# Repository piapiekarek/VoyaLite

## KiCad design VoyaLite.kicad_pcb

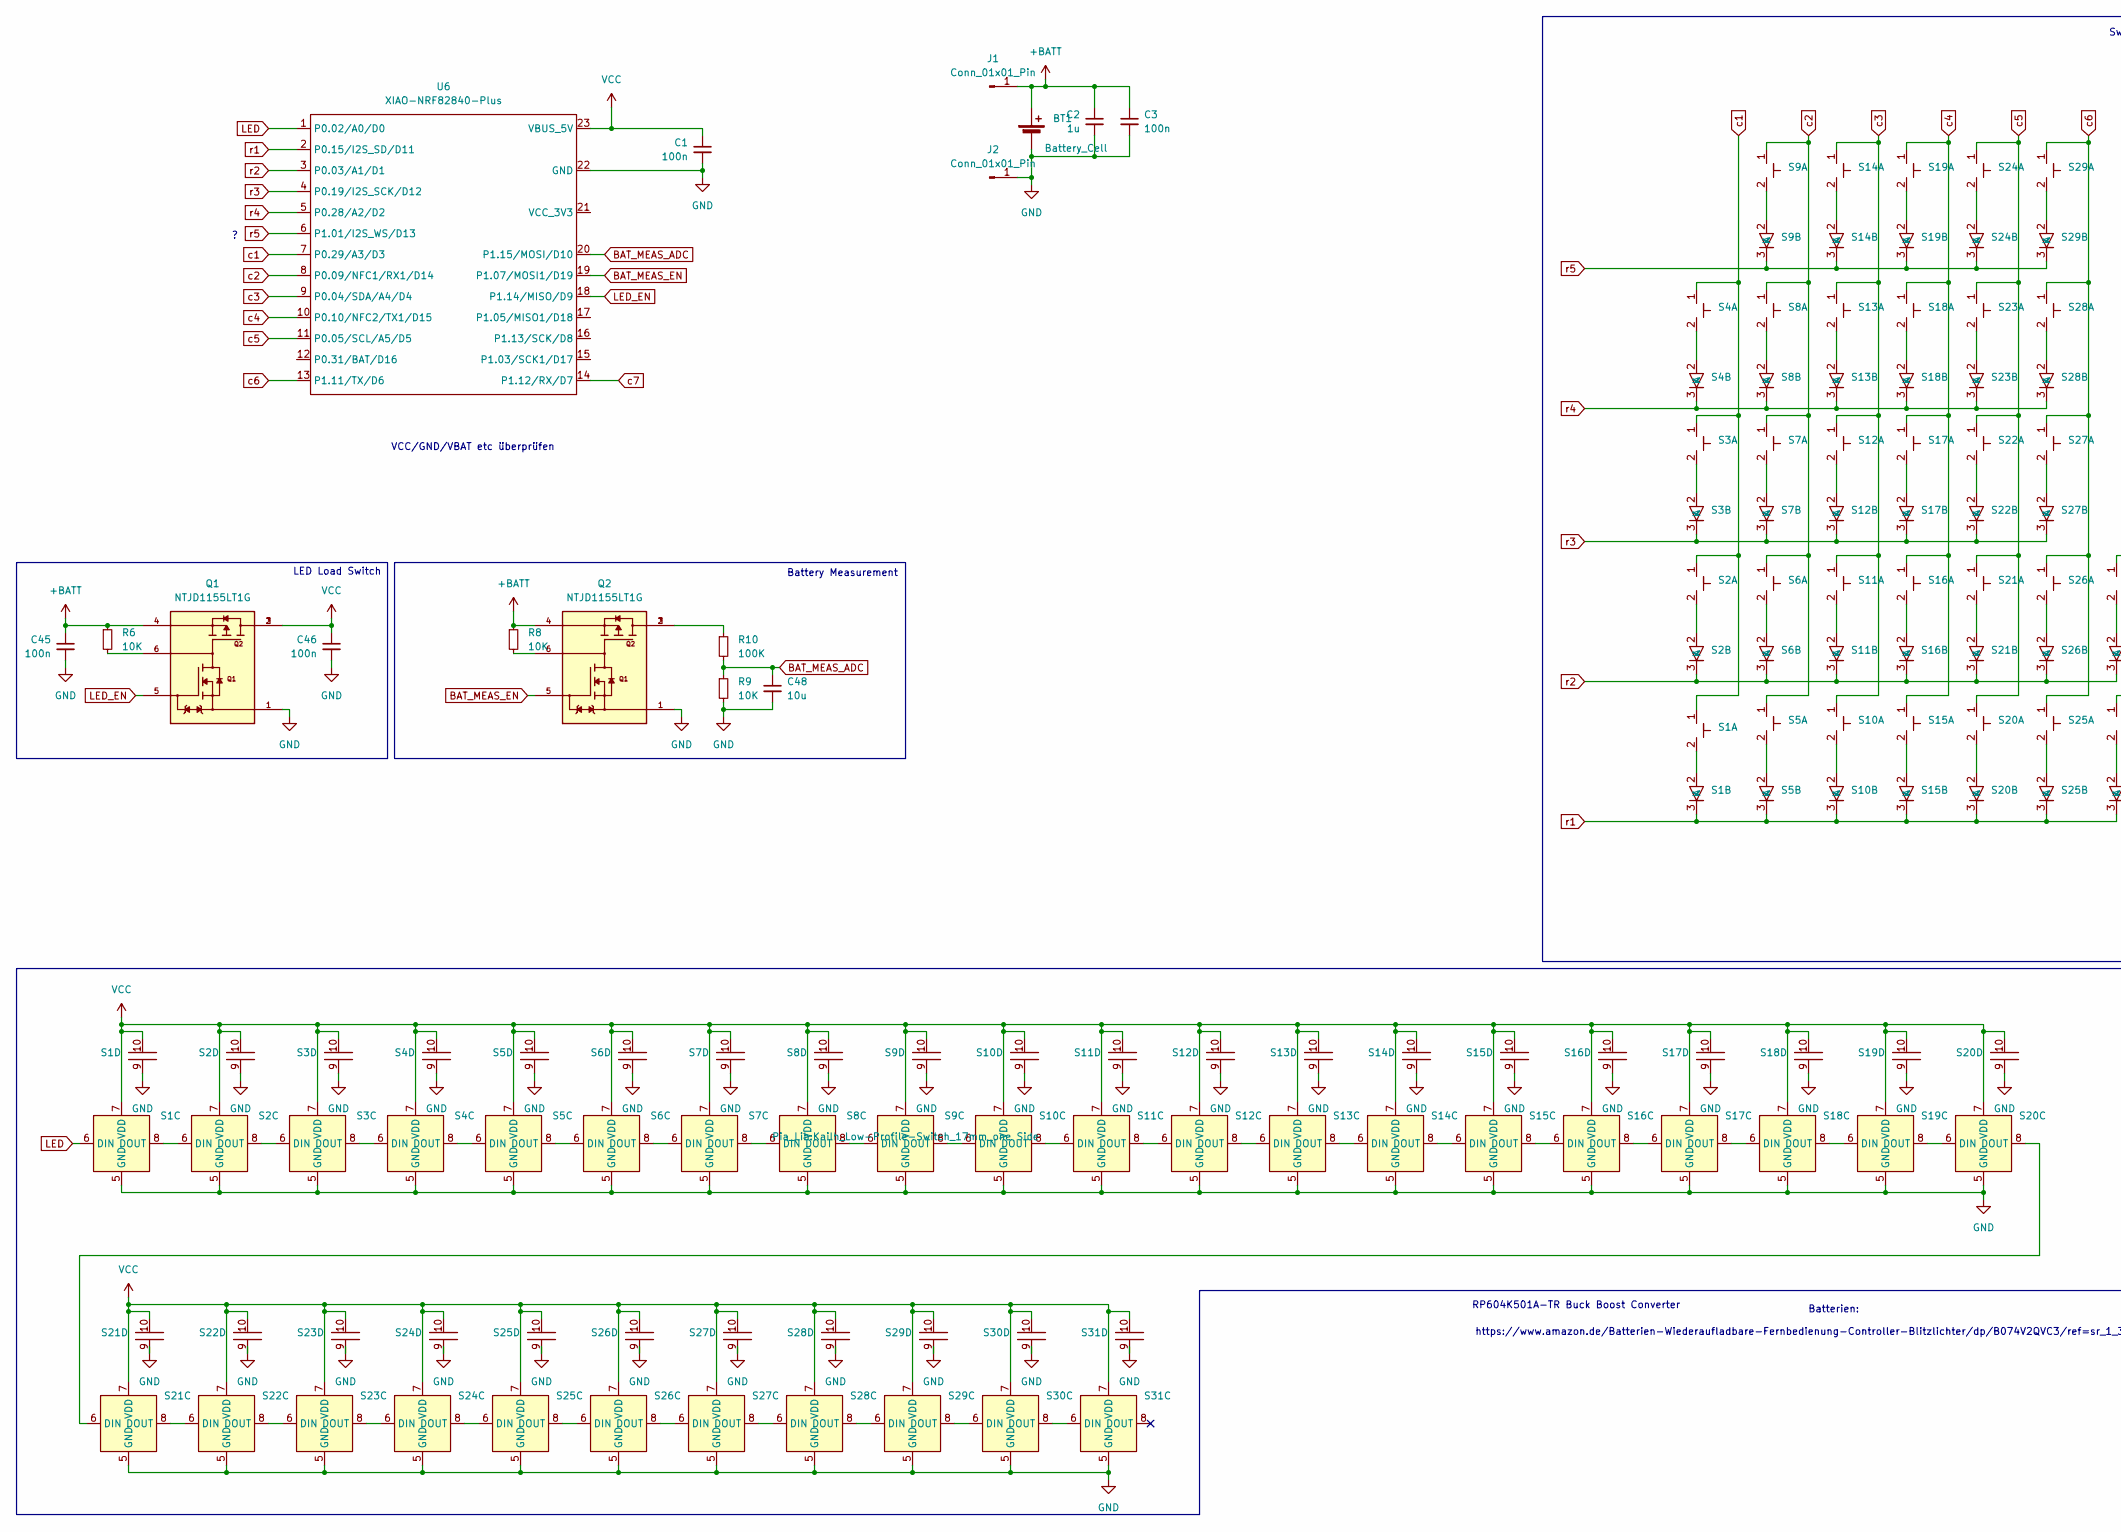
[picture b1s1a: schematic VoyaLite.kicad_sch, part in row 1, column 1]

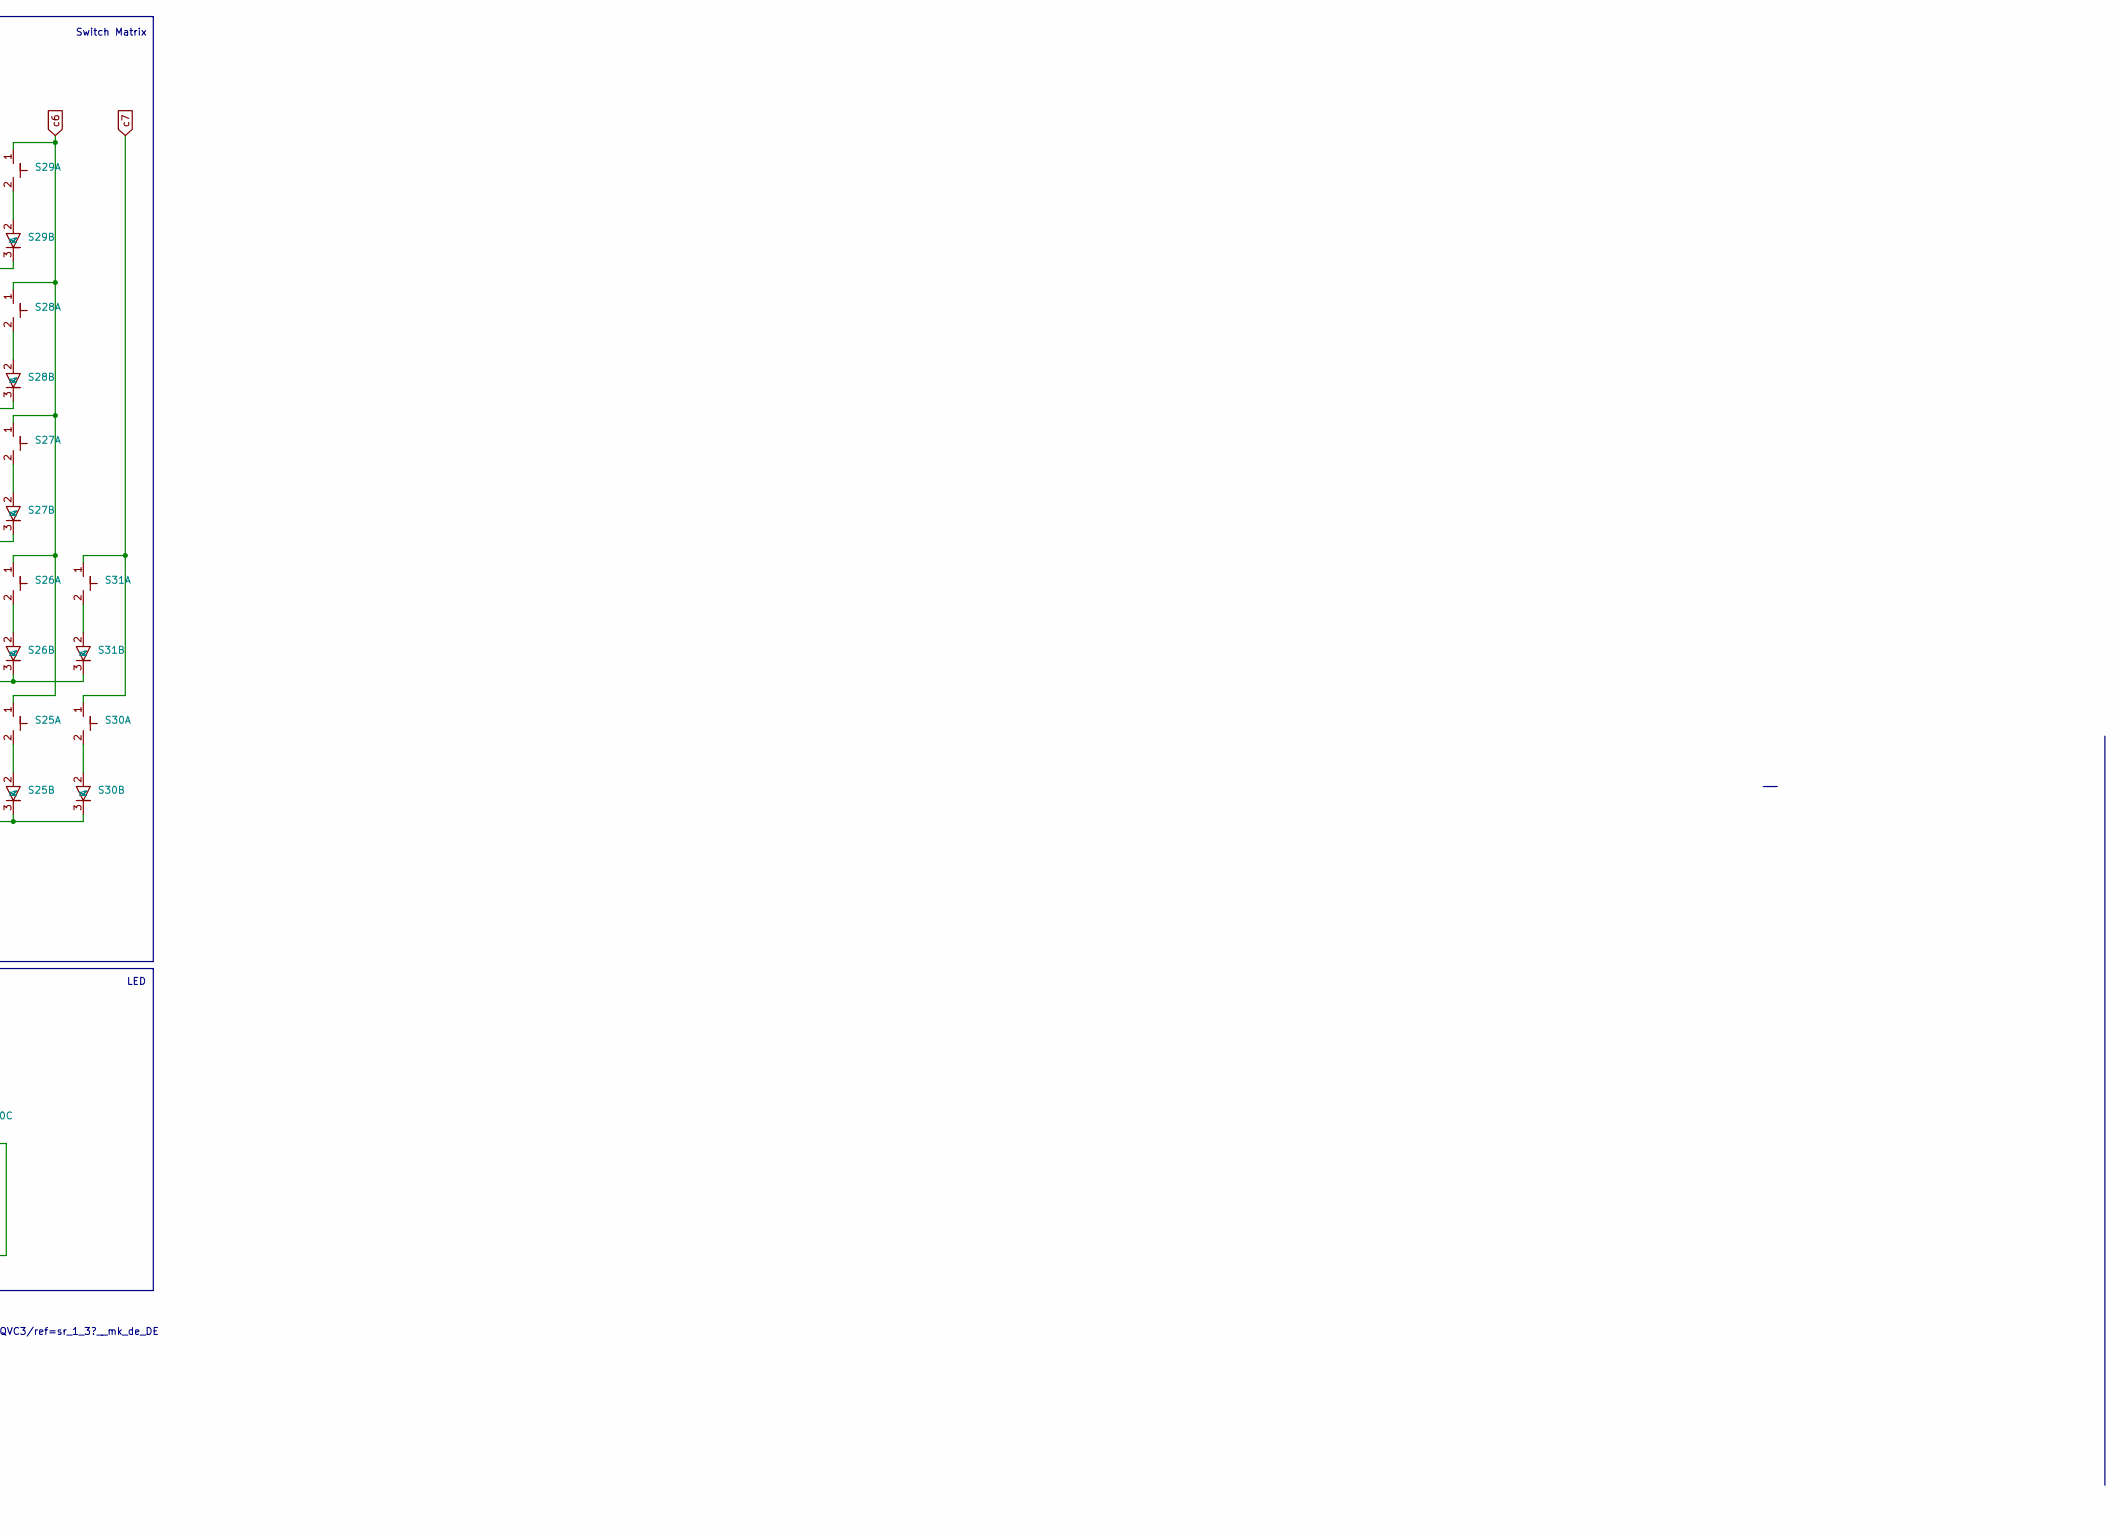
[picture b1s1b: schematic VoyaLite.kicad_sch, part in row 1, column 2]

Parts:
BT1: Battery_Cell; Batteriehalter AAA_Metall
C1, C3, C45, C46: 100n; C_0402_1005Metric_Pad0.74x0.62mm_HandSolder
C2: 1u; C_0402_1005Metric_Pad0.74x0.62mm_HandSolder
C48: 10u; C_0603_1608Metric_Pad1.08x0.95mm_HandSolder
J1, J2: Conn_01x01_Pin; Testpoint-pad
Q1, Q2: NTJD1155LT1G; TRANS_NTJD1155LT1G; PARTREV Rev. 6
R6, R8, R9: 10K; C_0402_1005Metric_Pad0.74x0.62mm_HandSolder
R10: 100K; C_0402_1005Metric_Pad0.74x0.62mm_HandSolder
S1, S2, S3, S4, S5, S6, S7, S8, S9, S10, S11, S12, S13, S14, S15, S16, S17, S18, S19, S20, S21, S22, S23, S24, S25, S26, S27, S28, S29, S30, S31: Kailh_Low-Profile-Switch_17mm_one Side
U6: XIAO-NRF82840-Plus; MCU_Seeed_nRF52840

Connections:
+BATT: BT1.1 (+), C2.1, C3.1, C45.1, J1.1, Q1.4, Q2.4, R6.1, R8.1
BAT_MEAS_ADC: C48.1, R9.1, R10.2, U6.20 (P1.15/MOSI/D10)
BAT_MEAS_EN: Q2.5, U6.19 (P1.07/MOSI1/D19)
GND: BT1.2 (-), C1.2, C2.2, C3.2, C45.2, C46.2, C48.2, J2.1, Q1.1, Q2.1, R9.2, S1.5 (GND), S1.9, S2.5 (GND), S2.9, S3.5 (GND), S3.9, S4.5 (GND), S4.9, S5.5 (GND), S5.9, S6.5 (GND), S6.9, S7.5 (GND), S7.9, S8.5 (GND), S8.9, S9.5 (GND), S9.9, S10.5 (GND), S10.9, S11.5 (GND), S11.9, S12.5 (GND), S12.9, S13.5 (GND), S13.9, S14.5 (GND), S14.9, S15.5 (GND), S15.9, S16.5 (GND), S16.9, S17.5 (GND), S17.9, S18.5 (GND), S18.9, S19.5 (GND), S19.9, S20.5 (GND), S20.9, S21.5 (GND), S21.9, S22.5 (GND), S22.9, S23.5 (GND), S23.9, S24.5 (GND), S24.9, S25.5 (GND), S25.9, S26.5 (GND), S26.9, S27.5 (GND), S27.9, S28.5 (GND), S28.9, S29.5 (GND), S29.9, S30.5 (GND), S30.9, S31.5 (GND), S31.9, U6.22 (GND)
LED: S1.6 (DIN), U6.1 (P0.02/A0/D0)
LED_EN: Q1.5, U6.18 (P1.14/MISO/D9)
unnamed: Q1.6, R6.2
unnamed: Q2.2, Q2.3, R10.1
unnamed: Q2.6, R8.2
unnamed: S1.8 (DOUT), S2.6 (DIN)
unnamed: S2.8 (DOUT), S3.6 (DIN)
unnamed: S3.8 (DOUT), S4.6 (DIN)
unnamed: S4.8 (DOUT), S5.6 (DIN)
unnamed: S5.8 (DOUT), S6.6 (DIN)
unnamed: S6.8 (DOUT), S7.6 (DIN)
unnamed: S7.8 (DOUT), S8.6 (DIN)
unnamed: S8.8 (DOUT), S9.6 (DIN)
unnamed: S9.8 (DOUT), S10.6 (DIN)
unnamed: S10.8 (DOUT), S11.6 (DIN)
unnamed: S11.8 (DOUT), S12.6 (DIN)
unnamed: S12.8 (DOUT), S13.6 (DIN)
unnamed: S13.8 (DOUT), S14.6 (DIN)
unnamed: S14.8 (DOUT), S15.6 (DIN)
unnamed: S15.8 (DOUT), S16.6 (DIN)
unnamed: S16.8 (DOUT), S17.6 (DIN)
unnamed: S17.8 (DOUT), S18.6 (DIN)
unnamed: S18.8 (DOUT), S19.6 (DIN)
unnamed: S19.8 (DOUT), S20.6 (DIN)
unnamed: S20.8 (DOUT), S21.6 (DIN)
unnamed: S21.8 (DOUT), S22.6 (DIN)
unnamed: S22.8 (DOUT), S23.6 (DIN)
unnamed: S23.8 (DOUT), S24.6 (DIN)
unnamed: S24.8 (DOUT), S25.6 (DIN)
unnamed: S25.8 (DOUT), S26.6 (DIN)
unnamed: S26.8 (DOUT), S27.6 (DIN)
unnamed: S27.8 (DOUT), S28.6 (DIN)
unnamed: S28.8 (DOUT), S29.6 (DIN)
unnamed: S29.8 (DOUT), S30.6 (DIN)
unnamed: S30.8 (DOUT), S31.6 (DIN)
VCC: C1.1, C46.1, Q1.2, Q1.3, S1.7 (VDD), S1.10, S2.7 (VDD), S2.10, S3.7 (VDD), S3.10, S4.7 (VDD), S4.10, S5.7 (VDD), S5.10, S6.7 (VDD), S6.10, S7.7 (VDD), S7.10, S8.7 (VDD), S8.10, S9.7 (VDD), S9.10, S10.7 (VDD), S10.10, S11.7 (VDD), S11.10, S12.7 (VDD), S12.10, S13.7 (VDD), S13.10, S14.7 (VDD), S14.10, S15.7 (VDD), S15.10, S16.7 (VDD), S16.10, S17.7 (VDD), S17.10, S18.7 (VDD), S18.10, S19.7 (VDD), S19.10, S20.7 (VDD), S20.10, S21.7 (VDD), S21.10, S22.7 (VDD), S22.10, S23.7 (VDD), S23.10, S24.7 (VDD), S24.10, S25.7 (VDD), S25.10, S26.7 (VDD), S26.10, S27.7 (VDD), S27.10, S28.7 (VDD), S28.10, S29.7 (VDD), S29.10, S30.7 (VDD), S30.10, S31.7 (VDD), S31.10, U6.23 (VBUS_5V)
c1: S1.1, S2.1, S3.1, S4.1, U6.7 (P0.29/A3/D3)
c2: S5.1, S6.1, S7.1, S8.1, S9.1, U6.8 (P0.09/NFC1/RX1/D14)
c3: S10.1, S11.1, S12.1, S13.1, S14.1, U6.9 (P0.04/SDA/A4/D4)
c4: S15.1, S16.1, S17.1, S18.1, S19.1, U6.10 (P0.10/NFC2/TX1/D15)
c5: S20.1, S21.1, S22.1, S23.1, S24.1, U6.11 (P0.05/SCL/A5/D5)
c6: S25.1, S26.1, S27.1, S28.1, S29.1, U6.13 (P1.11/TX/D6)
c7: S30.1, S31.1, U6.14 (P1.12/RX/D7)
r1: S1.3 (K), S5.3 (K), S10.3 (K), S15.3 (K), S20.3 (K), S25.3 (K), S30.3 (K), U6.2 (P0.15/I2S_SD/D11)
r2: S2.3 (K), S6.3 (K), S11.3 (K), S16.3 (K), S21.3 (K), S26.3 (K), S31.3 (K), U6.3 (P0.03/A1/D1)
r3: S3.3 (K), S7.3 (K), S12.3 (K), S17.3 (K), S22.3 (K), S27.3 (K), U6.4 (P0.19/I2S_SCK/D12)
r4: S4.3 (K), S8.3 (K), S13.3 (K), S18.3 (K), S23.3 (K), S28.3 (K), U6.5 (P0.28/A2/D2)
r5: S9.3 (K), S14.3 (K), S19.3 (K), S24.3 (K), S29.3 (K), U6.6 (P1.01/I2S_WS/D13)

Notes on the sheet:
VCC/GND/VBAT etc überprüfen
Battery Measurement
Batterien: https://www.amazon.de/Batterien-Wiederaufladbare-Fernbedienung-Controller-Blitzlichter/dp/B074V2QVC3/ref=sr_1_3?__mk_de_DE
LED Load Switch
LED
Switch Matrix
RP604K501A-TR Buck Boost Converter

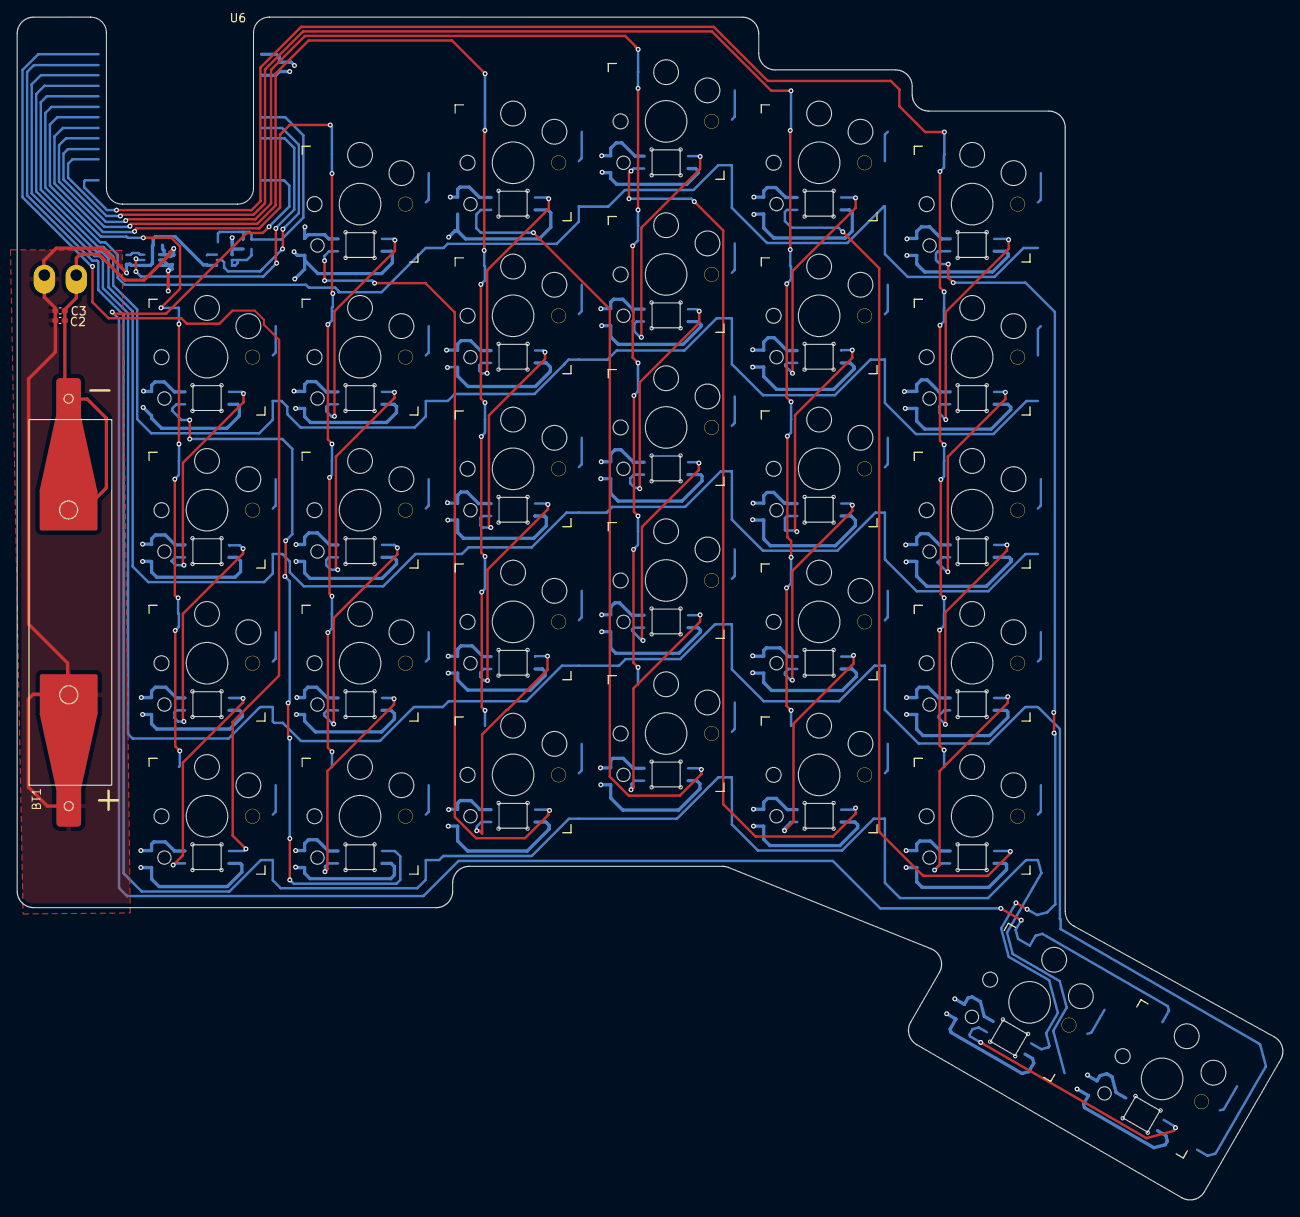
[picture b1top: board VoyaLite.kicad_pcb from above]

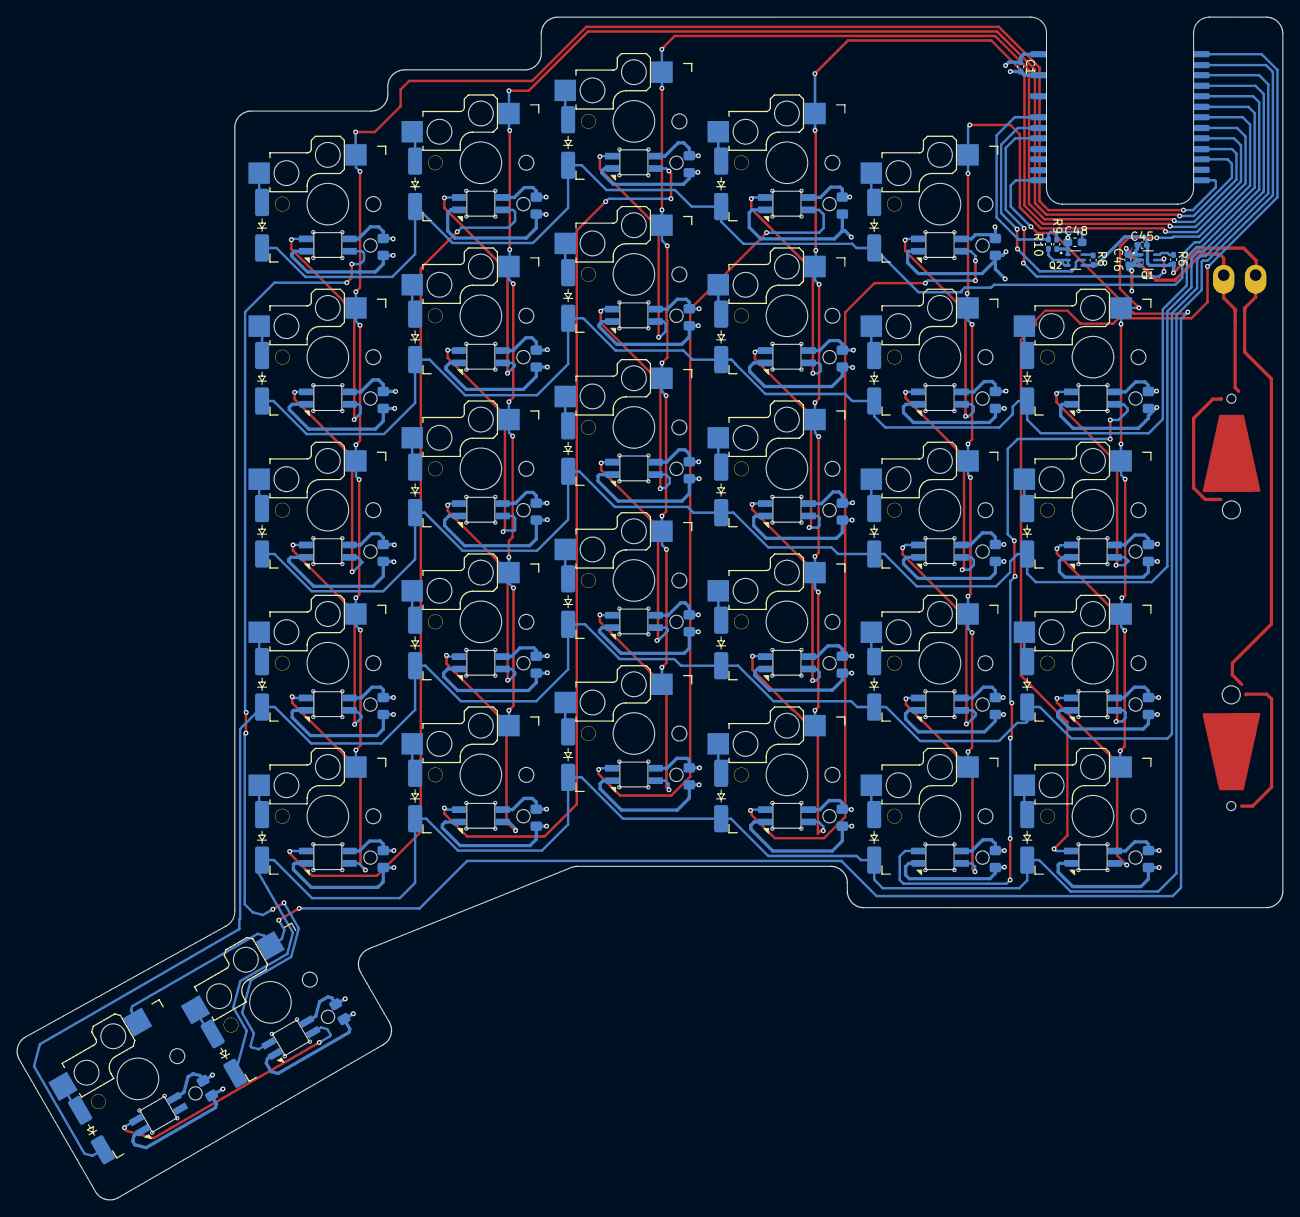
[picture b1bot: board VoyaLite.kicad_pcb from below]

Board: 4 copper layers, 153.0 x 143.0 mm, 47 parts (12 on the bottom side), 52 nets.

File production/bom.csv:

Designator,Footprint,Quantity,Value,LCSC Part #
BT1,Batteriehalter AAA_Metall,1,Battery_Cell,
"C1, C3, C45, C46",0402,4,100n,
C2,0402,1,1u,
C48,0603,1,10u,
"J1, J2",Testpoint-pad,2,Conn_01x01_Pin,
"Q1, Q2",TRANS_NTJD1155LT1G,2,NTJD1155LT1G,
R10,0402,1,100K,
"R6, R8, R9",0402,3,10K,
"S1, S10, S11, S12, S13, S14, S15, S16, S17, S18, S19, S2, S20, S21, S22, S23, S24, S25, S26, S27, S28, S29, S3, S30, S31, S4, S5, S6, S7, S8, S9",Kailh_Low-Profile-Switch_17mm_one Side,31,~,
U6,MCU_Seeed_nRF52840,1,XIAO-NRF82840-Plus,

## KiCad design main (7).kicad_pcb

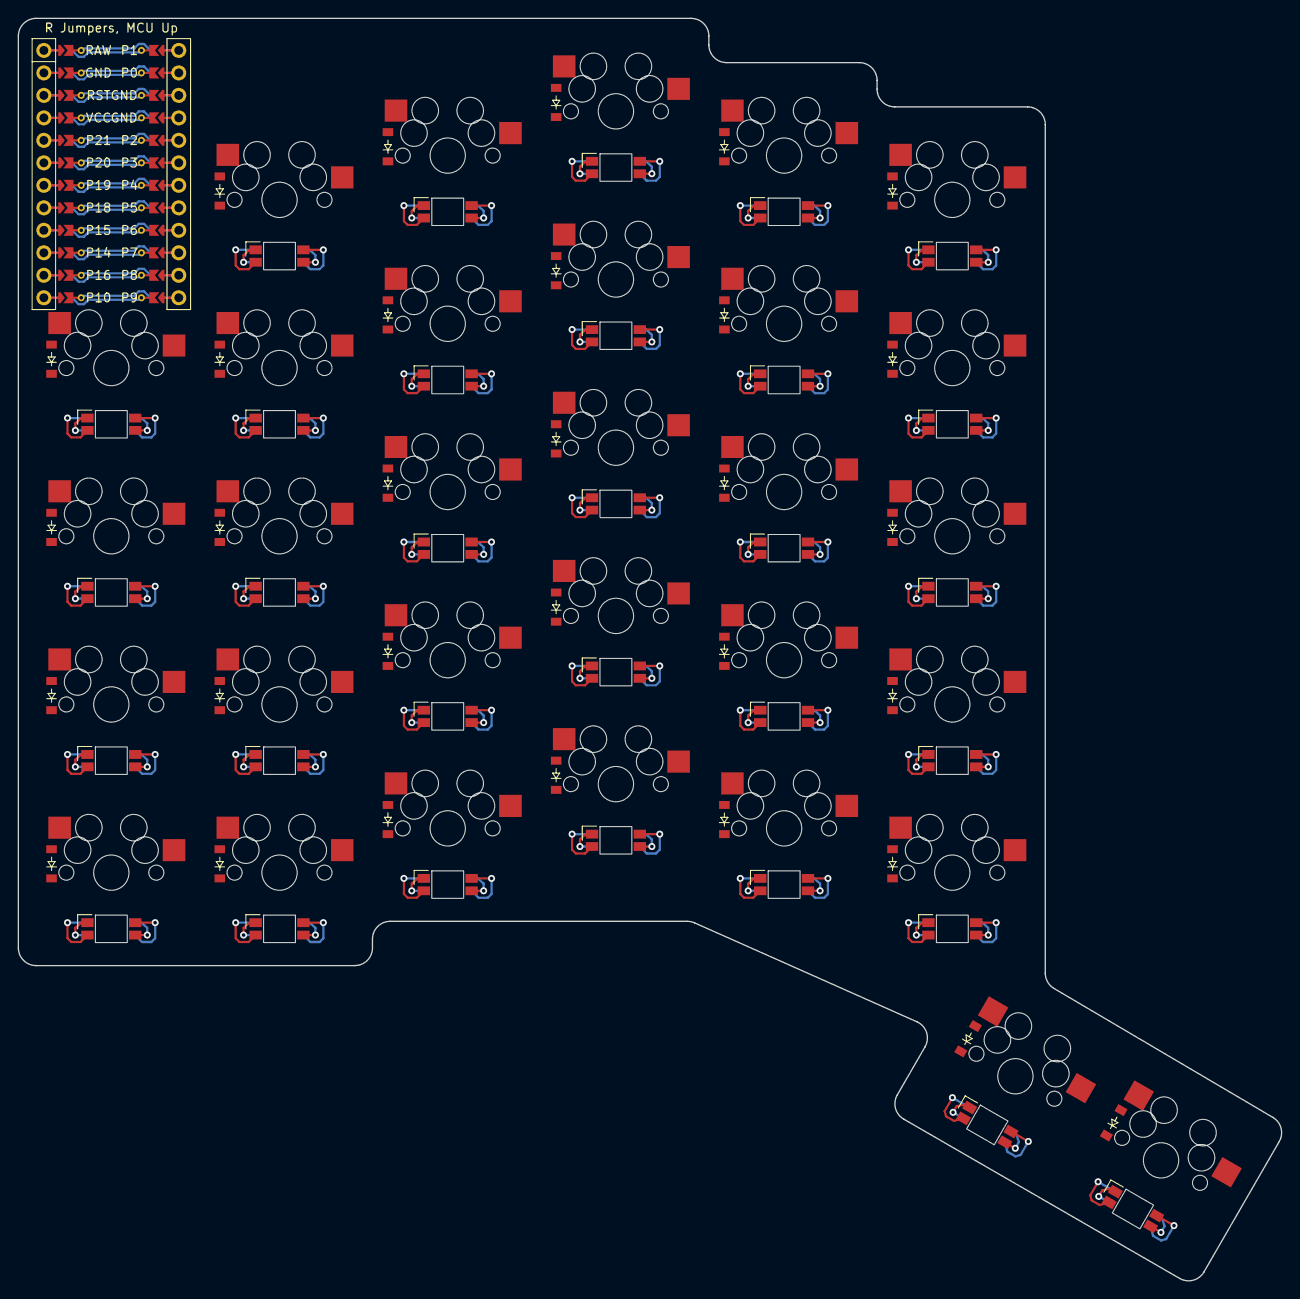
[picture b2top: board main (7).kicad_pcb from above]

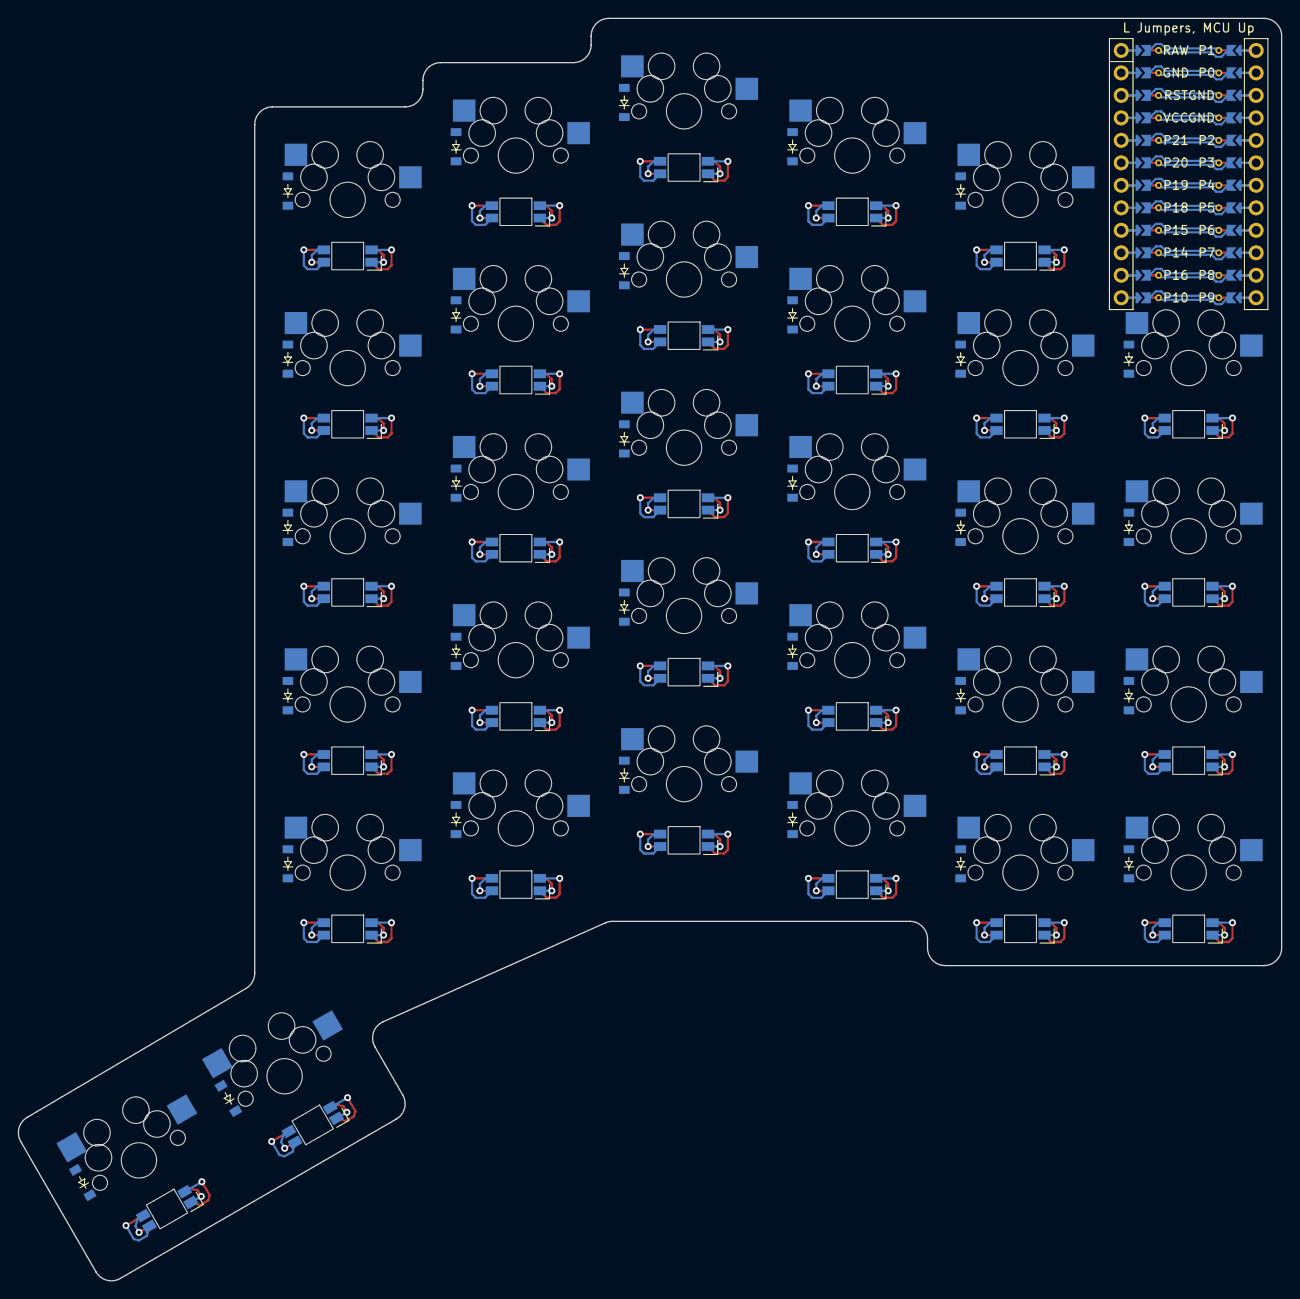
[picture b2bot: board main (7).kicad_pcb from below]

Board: 2 copper layers, 142.7 x 142.6 mm, 125 parts (62 on the bottom side), 69 nets.

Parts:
D1, D2, D3, D4, D5, D6, D7, D8, D9, D10, D11, D12, D13, D14, D15, D16, D17, D18, D19, D20, D21, D22, D23, D24, D25, D26, D27, D28, D29, D30, D31, D32, D33, D34, D35, D36, D37, D38, D39, D40, D41, D42, D43, D44, D45, D46, D47, D48, D49, D50, D51, D52, D53, D54, D55, D56, D57, D58, D59, D60, D61, D62: diode_tht_sod123
LED1, LED2, LED3, LED4, LED5, LED6, LED7, LED8, LED9, LED10, LED11, LED12, LED13, LED14, LED15, LED16, LED17, LED18, LED19, LED20, LED21, LED22, LED23, LED24, LED25, LED26, LED27, LED28, LED29, LED30, LED31: led_SK6812mini-e (underglow, reversible)
MCU1: mcu_nice_nano
S1, S2, S3, S4, S5, S6, S7, S8, S9, S10, S11, S12, S13, S14, S15, S16, S17, S18, S19, S20, S21, S22, S23, S24, S25, S26, S27, S28, S29, S30, S31: MX

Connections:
GND: LED1.3, LED2.3, LED3.3, LED4.3, LED5.3, LED6.3, LED7.3, LED8.3, LED9.3, LED10.3, LED11.3, LED12.3, LED13.3, LED14.3, LED15.3, LED16.3, LED17.3, LED18.3, LED19.3, LED20.3, LED21.3, LED22.3, LED23.3, LED24.3, LED25.3, LED26.3, LED27.3, LED28.3, LED29.3, LED30.3, LED31.3, MCU1.103, MCU1.104, MCU1.123
LED_2: LED1.2, LED2.4
LED_3: LED2.2, LED3.4
LED_4: LED3.2, LED4.4
LED_5: LED4.2, LED5.4
LED_6: LED5.2, LED6.4
LED_7: LED6.2, LED7.4
LED_8: LED7.2, LED8.4
LED_9: LED8.2, LED9.4
LED_10: LED9.2, LED10.4
LED_11: LED10.2, LED11.4
LED_12: LED11.2, LED12.4
LED_13: LED12.2, LED13.4
LED_14: LED13.2, LED14.4
LED_15: LED14.2, LED15.4
LED_16: LED15.2, LED16.4
LED_17: LED16.2, LED17.4
LED_18: LED17.2, LED18.4
LED_19: LED18.2, LED19.4
LED_20: LED19.2, LED20.4
LED_21: LED20.2, LED21.4
LED_22: LED21.2, LED22.4
LED_23: LED22.2, LED23.4
LED_24: LED23.2, LED24.4
LED_25: LED24.2, LED25.4
LED_26: LED25.2, LED26.4
LED_27: LED26.2, LED27.4
LED_28: LED27.2, LED28.4
LED_29: LED28.2, LED29.4
LED_30: LED29.2, LED30.4
LED_31: LED30.2, LED31.4
VCC: LED1.1, LED2.1, LED3.1, LED4.1, LED5.1, LED6.1, LED7.1, LED8.1, LED9.1, LED10.1, LED11.1, LED12.1, LED13.1, LED14.1, LED15.1, LED16.1, LED17.1, LED18.1, LED19.1, LED20.1, LED21.1, LED22.1, LED23.1, LED24.1, LED25.1, LED26.1, LED27.1, LED28.1, LED29.1, LED30.1, LED31.1, MCU1.121
c1_r2: D4.2, D35.2, S4.2
c1_r3: D3.2, D34.2, S3.2
c1_r4: D2.2, D33.2, S2.2
c1_r5: D1.2, D32.2, S1.2
c2_r1: D9.2, D40.2, S9.2
c2_r2: D8.2, D39.2, S8.2
c2_r3: D7.2, D38.2, S7.2
c2_r4: D6.2, D37.2, S6.2
c2_r5: D5.2, D36.2, S5.2
c3_r1: D14.2, D45.2, S14.2
c3_r2: D13.2, D44.2, S13.2
c3_r3: D12.2, D43.2, S12.2
c3_r4: D11.2, D42.2, S11.2
c3_r5: D10.2, D41.2, S10.2
c4_r1: D19.2, D50.2, S19.2
c4_r2: D18.2, D49.2, S18.2
c4_r3: D17.2, D48.2, S17.2
c4_r4: D16.2, D47.2, S16.2
c4_r5: D15.2, D46.2, S15.2
c5_r1: D24.2, D55.2, S24.2
c5_r2: D23.2, D54.2, S23.2
c5_r3: D22.2, D53.2, S22.2
c5_r4: D21.2, D52.2, S21.2
c5_r5: D20.2, D51.2, S20.2
c6_r1: D29.2, D60.2, S29.2
c6_r2: D28.2, D59.2, S28.2
c6_r3: D27.2, D58.2, S27.2
c6_r4: D26.2, D57.2, S26.2
c6_r5: D25.2, D56.2, S25.2
cluster: D30.1, D31.1, D61.1, D62.1
layer_cluster: D30.2, D61.2, S30.2
r1: D9.1, D14.1, D19.1, D24.1, D29.1, D40.1, D45.1, D50.1, D55.1, D60.1
r2: D4.1, D8.1, D13.1, D18.1, D23.1, D28.1, D35.1, D39.1, D44.1, D49.1, D54.1, D59.1
r3: D3.1, D7.1, D12.1, D17.1, D22.1, D27.1, D34.1, D38.1, D43.1, D48.1, D53.1, D58.1
r4: D2.1, D6.1, D11.1, D16.1, D21.1, D26.1, D33.1, D37.1, D42.1, D47.1, D52.1, D57.1
r5: D1.1, D5.1, D10.1, D15.1, D20.1, D25.1, D32.1, D36.1, D41.1, D46.1, D51.1, D56.1
space_cluster: D31.2, D62.2, S31.2

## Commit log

2024-11-06 second commit
2024-12-19 change things
2025-01-02 add Traces to pcb
2025-01-09 add tracks
2025-01-22 add voyalite
2025-07-16 add changes to voyalite. Add nrf52840 plus
2025-10-29 add newer files
2025-10-30 add changes
2025-11-03 add final changes
2025-11-12 add new production files
